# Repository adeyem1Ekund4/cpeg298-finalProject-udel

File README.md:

# Internet of Things Device for Humidity Sensor: Iot THS
The primary goal of the project is to read temperature and humidity data from the DHT20 sensor, process this data, and then send it to a server or cloud service (implied by the Adafruit IO setup) via the ESP8266.
# Schematic

# THS PCB View
### Front

### Back

# Arduino Code
The code sets up various parameters such as WiFi credentials, pins for LEDs, temperature thresholds, and initializes the DHT20 sensor.

In the setup() function:

The DHT20 sensor is initialized.
Pins 12 and 13 are set as output pins for LEDs.
Serial communication is started at a baud rate of 9600.
The ESP8266 module is initialized using software serial communication.
Various commands are sent to the ESP8266 module to set up WiFi connection, Adafruit IO credentials, and start the IoT connection.
If the connection to Adafruit IO fails, the program enters an infinite loop.
In the loop() function:

The code reads data from the DHT20 sensor every second.
The temperature and humidity values are obtained from the sensor.
The temperature value is sent to the ESP8266 module for further processing.
Based on the humidity level, different LED patterns are displayed.
The sensor data along with the status of the sensor reading is printed to the serial monitor.
The espData() function is used to send commands to the ESP8266 module and receive responses. It waits for a response within a specified timeout period and returns the response as a string.

# Adafruit Hub

# Future Changes
For the program, to improve readability and maintainability, break down the code into multiple functions, such as moving LED control logic into a separate function. Avoid using delays in the loop, as they can block other operations and affect system responsiveness. Improve error handling, especially for Wi-Fi and Adafruit IO connections, and provide alternative actions or retries in case of failure. Avoid hardcoding sensitive information and consider external methods for secure input. Restructure the espData function to be more efficient and reliable, and implement a feedback mechanism from the server/cloud to the Arduino for more interactive control. For battery-operated projects, use power-saving techniques to extend battery life. Add checks to ensure data read from the DHT20 sensor is within reasonable bounds before sending it to avoid transmitting erroneous data.

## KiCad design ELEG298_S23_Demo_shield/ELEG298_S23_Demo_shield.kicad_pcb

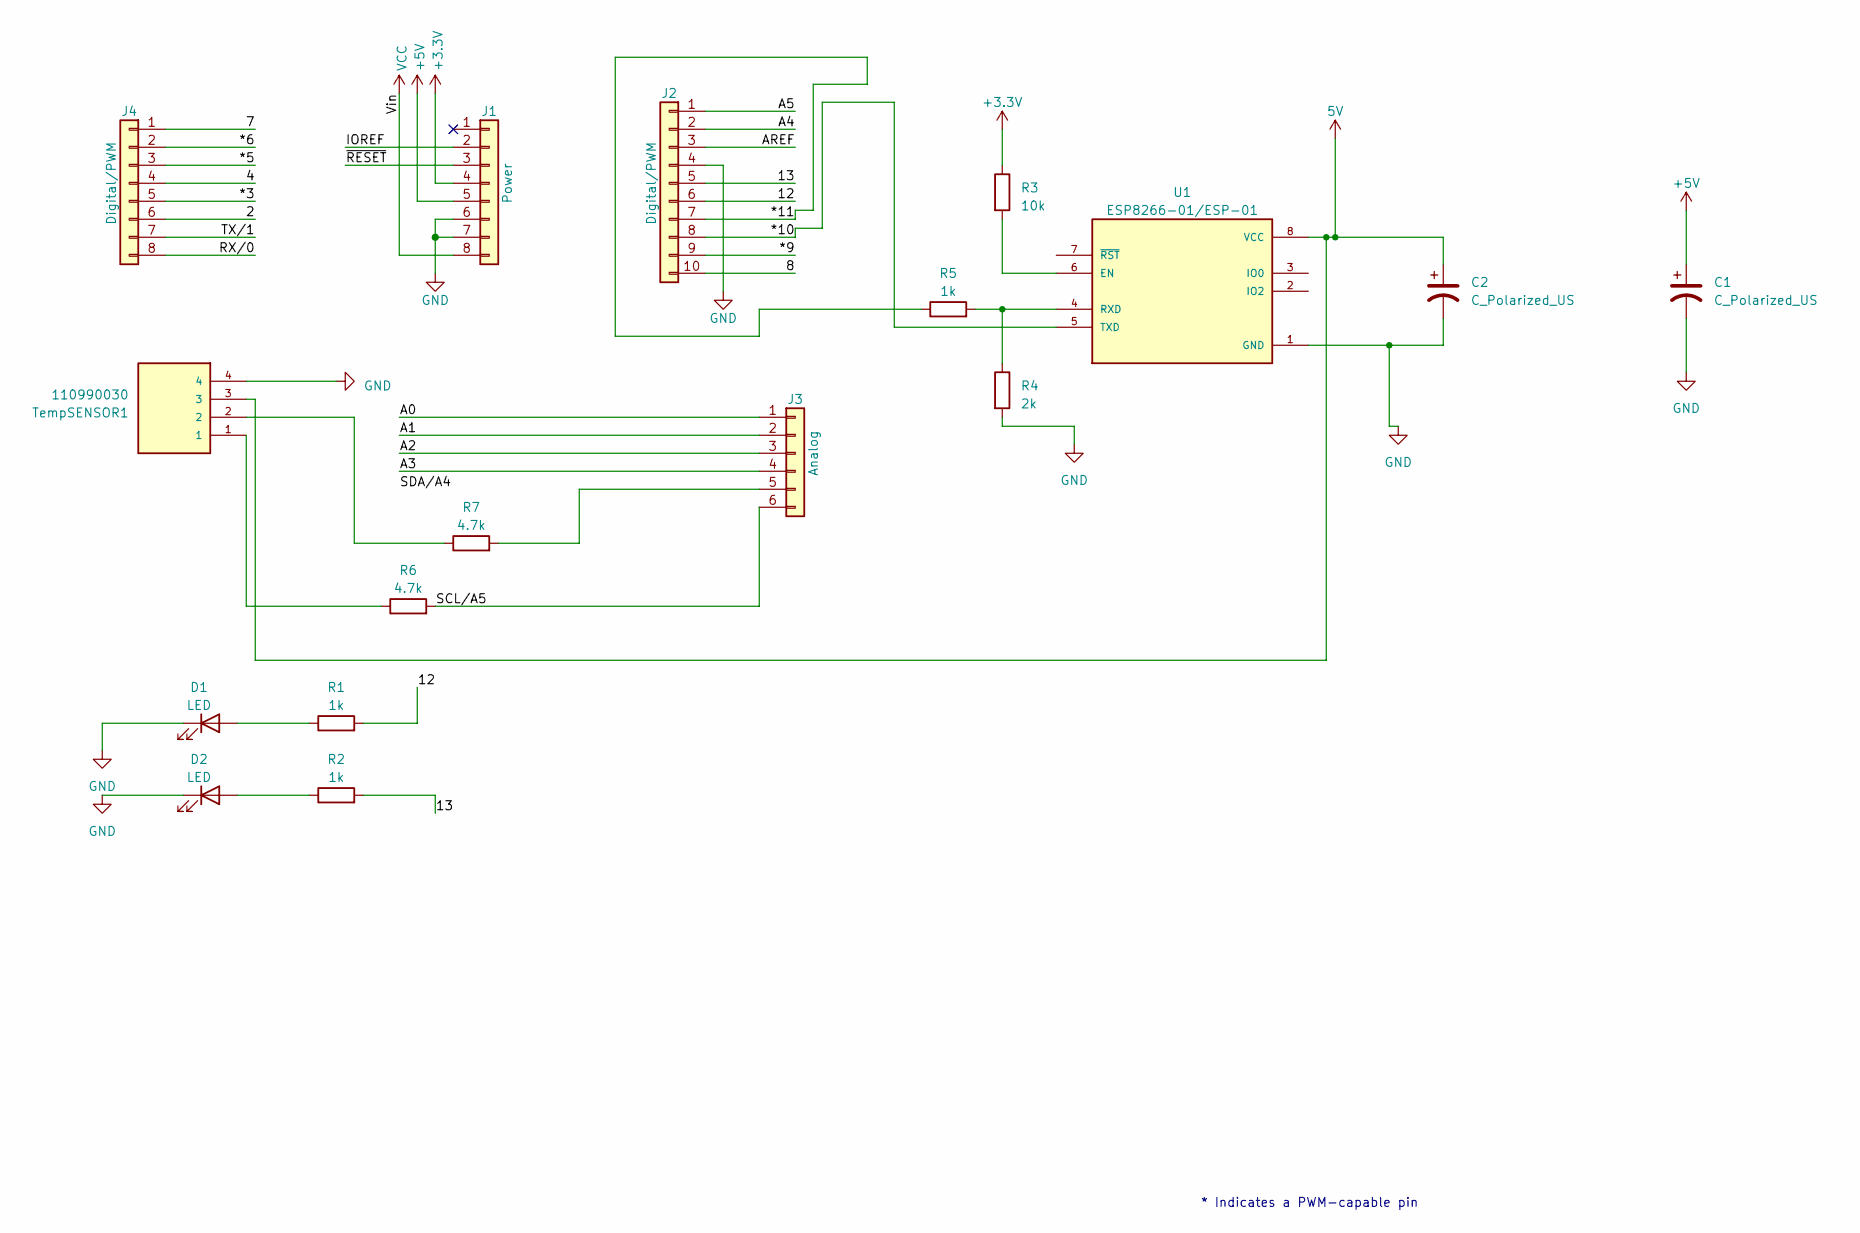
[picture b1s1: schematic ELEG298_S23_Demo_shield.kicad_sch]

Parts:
C1, C2: C_Polarized_US; CP_Radial_D6.3mm_P2.50mm
D1, D2: LED; LED_D5.0mm
J1: Power; PinSocket_1x08_P2.54mm_Vertical
J2: Digital/PWM; PinSocket_1x10_P2.54mm_Vertical
J3: Analog; PinSocket_1x06_P2.54mm_Vertical
J4: Digital/PWM; PinSocket_1x08_P2.54mm_Vertical
R1, R2, R5: 1k; R_Axial_DIN0207_L6.3mm_D2.5mm_P10.16mm_Horizontal
R3: 10k; R_Axial_DIN0207_L6.3mm_D2.5mm_P10.16mm_Horizontal
R4: 2k; R_Axial_DIN0207_L6.3mm_D2.5mm_P10.16mm_Horizontal
R6, R7: 4.7k; R_Axial_DIN0207_L6.3mm_D2.5mm_P10.16mm_Horizontal
TempSENSOR1: 110990030; SEEED_110990030; PARTREV A
U1: ESP8266-01/ESP-01; XCVR_ESP8266-01_ESP-01; PARTREV V1.2

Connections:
/2: J4.6
/4: J4.4
/7: J4.1
/8: J2.10
/12: J2.6, R1.2
/13: J2.5, R2.2
/*3: J4.5
/*5: J4.3
/*6: J4.2
/*9: J2.9
/*10: J2.8, U1.5 (TXD)
/*11: J2.7, R5.1
/A0: J3.1
/A1: J3.2
/A2: J3.3
/A3: J3.4
/A4: J2.2
/A5: J2.1
/AREF: J2.3
/IOREF: J1.2
/RX/0: J4.8
/SCL/A5: J3.6, R6.2
/TX/1: J4.7
/~RESET: J1.3
GND: C1.2, C2.2, D1.1 (K), D2.1 (K), J1.6, J1.7, J2.4, R4.2, TempSENSOR1.4, U1.1 (GND)
unnamed: D1.2 (A), R1.1
unnamed: D2.2 (A), R2.1
unnamed: J3.5, R7.2
unnamed: R6.1, TempSENSOR1.1
unnamed: R7.1, TempSENSOR1.2
unnamed: R3.2, U1.6 (EN)
unnamed: R4.1, R5.2, U1.4 (RXD)
VCC: J1.8

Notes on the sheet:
* Indicates a PWM-capable pin

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
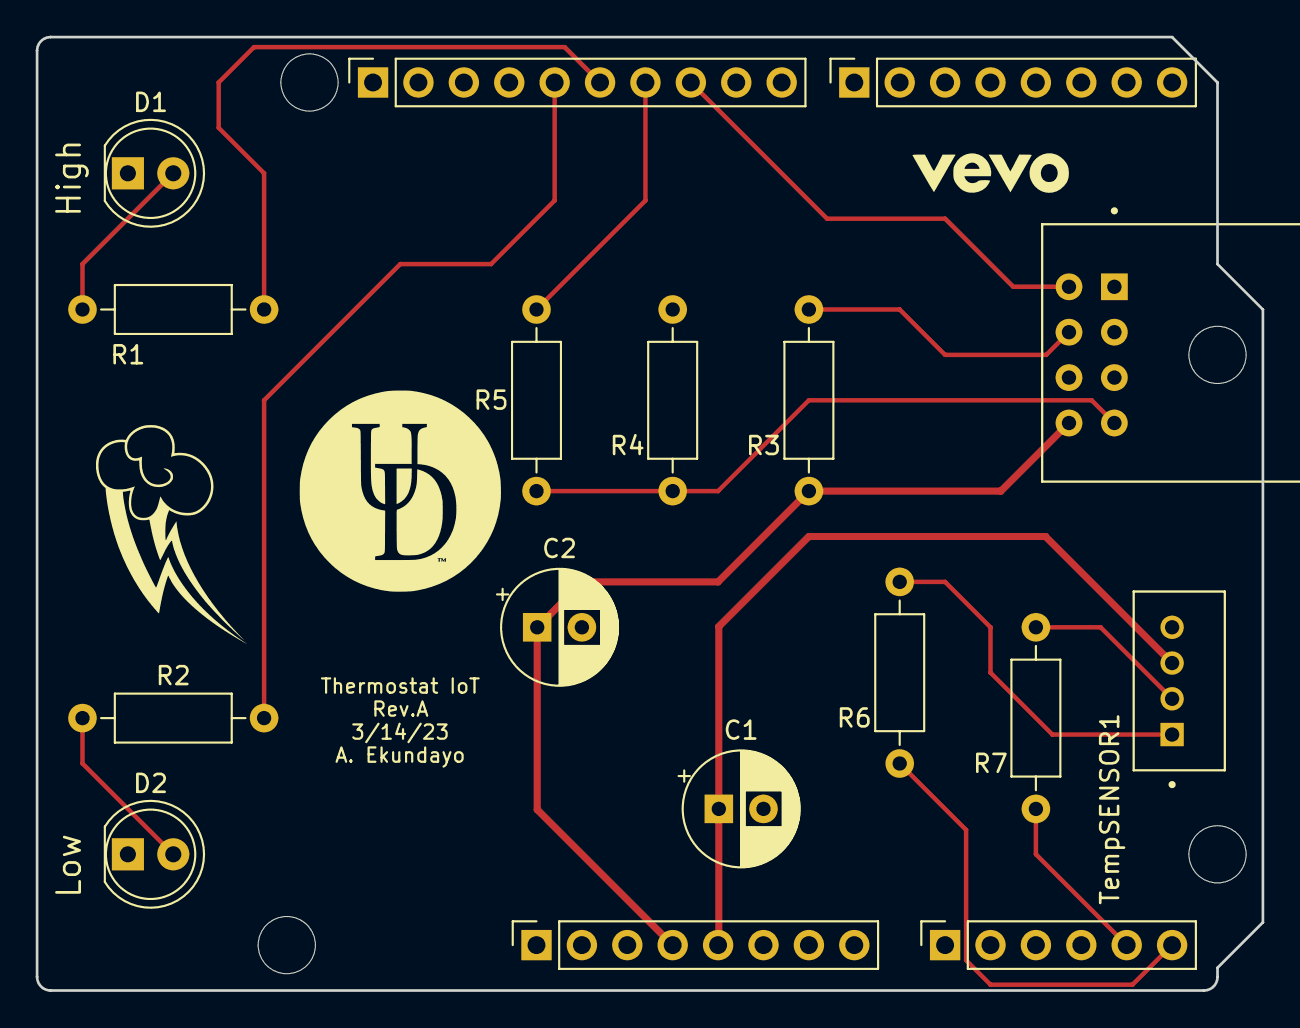
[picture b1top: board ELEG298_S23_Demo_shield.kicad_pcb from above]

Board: 2 copper layers, 68.6 x 53.3 mm, 21 parts (0 on the bottom side), 15 nets.

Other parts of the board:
MH1, MH2, MH3, MH4: MountingHole_3.2mm
